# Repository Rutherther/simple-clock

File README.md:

# Simple clock
This is just a small project that aims to make a simple clock, using STM32F103C8T6.
The clock will be shown on a seven segment display. There will be multiple modes to show
on the clock display.

## HW
STM32F103C8T6 is used as the _brains_. It has RTC that may be powered by CR2032 battery.
It's connected to a USB header, allowing to communicate with a computer. The chip is capable
of being a device, only, not host.
There is a header with 3V3, SWDIO, SWCLK, GND to allow programming the chip using a tool such as STLink.
ASM1117-3.3 is used for stepping down from 5V to 3V3.
3V3 should not be connected whilst USB is connected as well. This would short output of the LDO to 3V3.
There is no protection!

There are 8 seven segment displays,
4 of them are blue, 4 of them are yellow, the whole display looks like this: Y.Y.BB:BBY.Y.
(Y for yellow digit, B for blue digit)
There are 4 LEDs and 4 buttons, the LEDs are next to the buttons, making each LED "associated" with a button.
That makes it possible to light up an LED next to button, if the button is pressed etc.

The digits of the seven segment display are connected to PNP transistors.
When pulling the pin connected to the transistor low, the digit is turned on.
The pins used may be connected to timers, and PWM may be utilized to set
brightness.
Segments get turned on by being low as well.

Mapping of pins to peripherals is documented in [pins](docs/pins.md).

## Features / Roadmap

- [x] Remember date, time
  - [x] Time
  - [x] Date
- [x] Set time and date using simple interface
- [x] Switch between view modes by button
- [x] Show time, date
- [x] Adjust brightness using PWM
- [x] Auto adjust brightness based on time
- [ ] Stopwatch
- [ ] USB communication
  - [ ] Set time, Get time
  - [ ] Show arbitrary text or number on the display
  - [ ] Start stopwatch
  
## Usage
The clock has two modes, default mode, and edit mode.
Default mode displays the current time, edit mode is
for editing the current time.

### Default mode
This is entered upon reset. Upon startup,
it displays only current time as hours and minutes.

First button may change the current view, there are
four views.
1. time - hours and minutes only
2. time - with seconds
3. time and date - hours, minutes, day in month and month
4. date - year, day in month and month

The second button switches to edit mode.

Third and fourth buttons change brightness.
The brightness is normally automatically adjusted
based on the current time set on the clock.
It may be temporarily changed using these buttons.
The change will last 30 minutes.
Third button decreases brightness, fourth increases it.

### Edit mode
In the edit mode, it's possible to change the time and date.
Upon entering edit mode, hours will be selected to be changed.

The currently selected field will blink. To select the next field,
the first button should be used. The order of the fields edited is:
hours, minutes, seconds, year, month, day.

To increment or decrement the current field, second and third
buttons should be used, respectively.

To save the time and date, fourth button does the job.
It may be pressed when editing any field.

When in the edit mode, the time is paused. If you enter the
edit mode by accident, the clock will probably get behind,
because a couple of seconds will pass before you exit the edit mode.

## Images of the clock
### Front, off

### Back

### Front, with seconds

### Front, with clock and date

## What's next
Unfortunately, I did not solder the USB correctly on my board, so I cannot
currently test sending and receiving data using the USB, that is the reason
why the current program does not even support USB. In the future, the firmware
should support USB communication and a program for a computer should be made,
with some kind of CLI for communication with the board.

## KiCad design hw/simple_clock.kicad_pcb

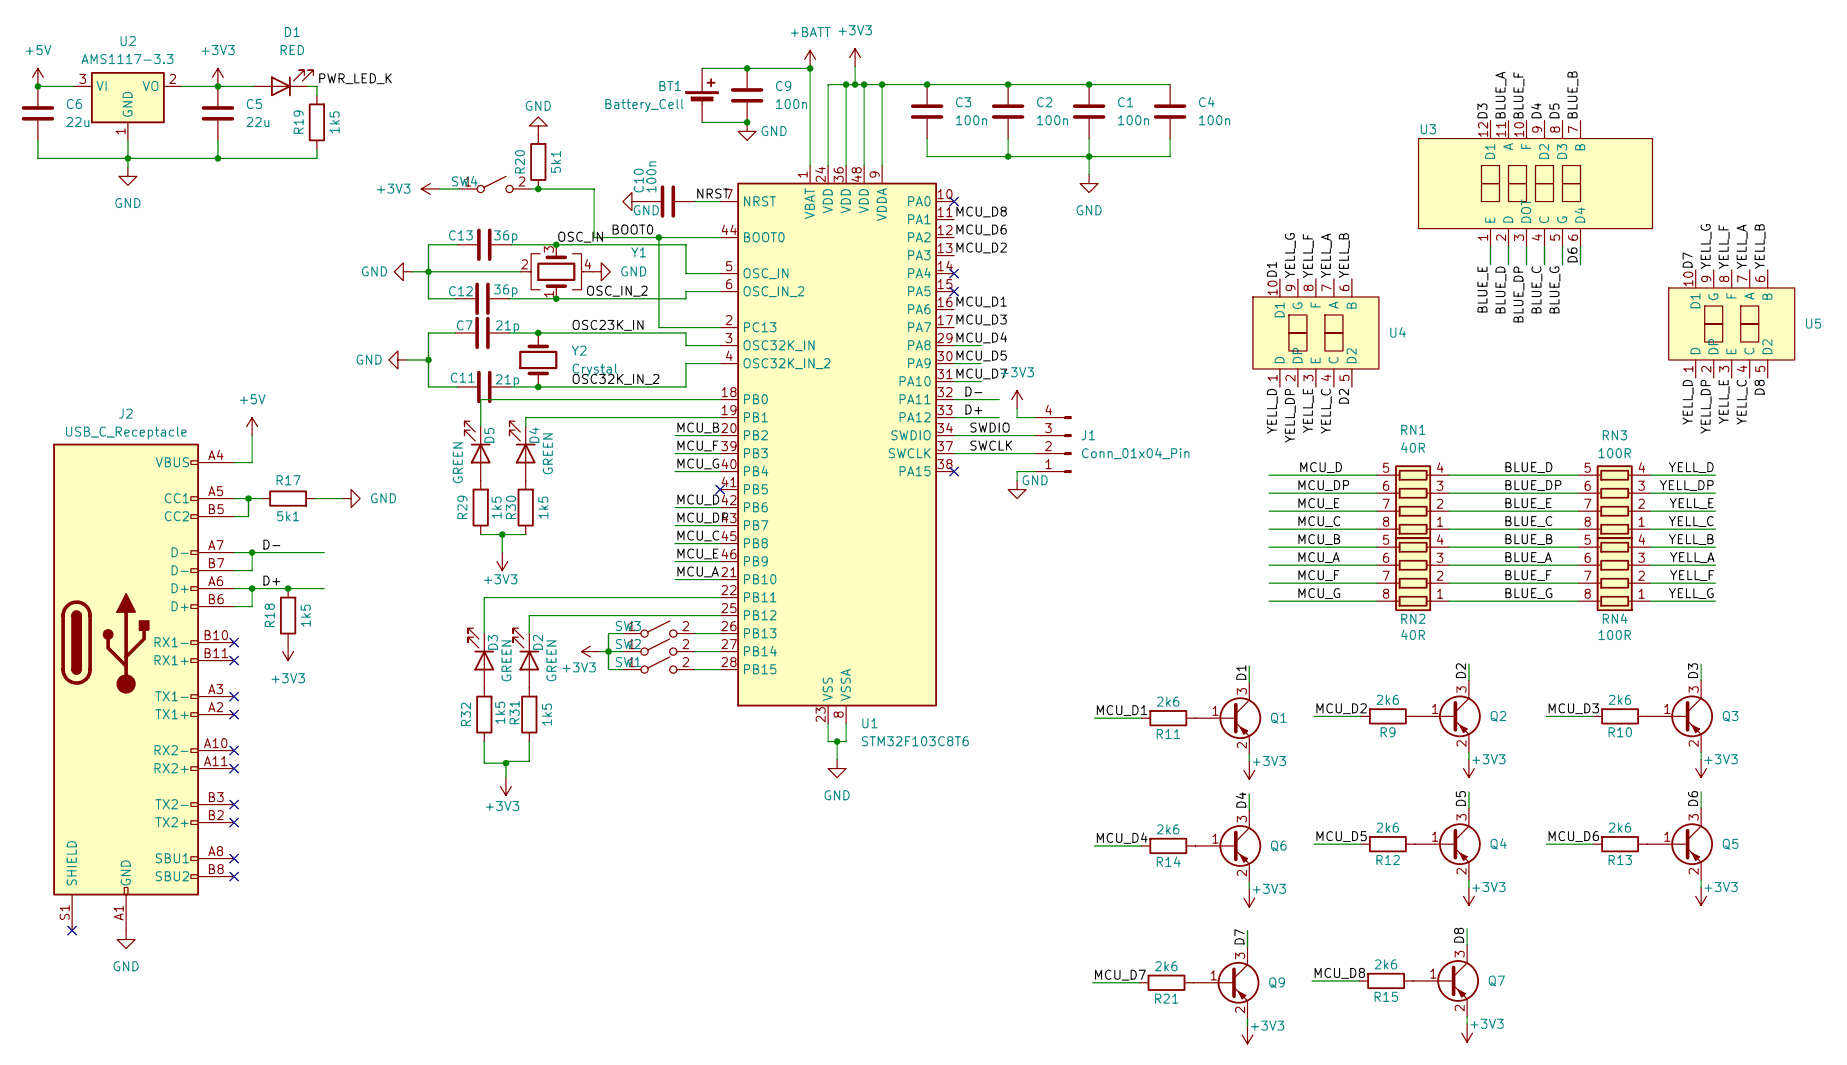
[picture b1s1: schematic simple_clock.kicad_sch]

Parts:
BT1: Battery_Cell; Q&J BS-8-1
C1, C2, C3, C4, C9, C10: 100n; C_0603_1608Metric
C5, C6: 22u; C_0603_1608Metric
C7, C11: 21p; C_0603_1608Metric
C12, C13: 36p; C_0603_1608Metric
D1: RED; LED_0603_1608Metric
D2, D3, D4, D5: GREEN; LED_0603_1608Metric
J1: Conn_01x04_Pin; PinHeader_1x04_P2.54mm_Vertical
J2: USB_C_Receptacle; USB_C_Receptacle_XKB_U262-16XN-4BVC11
Q1, Q2, Q3, Q4, Q5, Q6, Q7, Q9: Q_PNP_BEC; SOT-23
R9, R10, R11, R12, R13, R14, R15, R21: 2k6; R_0603_1608Metric
R17, R20: 5k1; R_0603_1608Metric
R18, R19, R29, R30, R31, R32: 1k5; R_0603_1608Metric
RN1, RN2: 40R; R_Array_Concave_4x0603
RN3, RN4: 100R; R_Array_Concave_4x0603
SW1, SW2, SW3, SW4: SW_SPST; TS-1088-AR02016
U1: STM32F103C8T6; LQFP-48_7x7mm_P0.5mm
U2: AMS1117-3.3; SOT-223-3_TabPin2
U3: SLR0404DBA2BD
U4, U5: SLR0402DYA3BD
Y1: Crystal_GND24; Crystal_SMD_3225-4Pin_3.2x2.5mm
Y2: Crystal; Crystal_SMD_3215-2Pin_3.2x1.5mm

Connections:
+3V3: C1.1, C2.1, C3.1, C4.1, C5.1, D1.2 (A), J1.4, Q1.2 (E), Q2.2 (E), Q3.2 (E), Q4.2 (E), Q5.2 (E), Q6.2 (E), Q7.2 (E), Q9.2 (E), R18.1, R29.1, R30.1, R31.1, R32.1, SW1.1 (A), SW2.1 (A), SW3.1 (A), SW4.1 (A), U1.9 (VDDA), U1.24 (VDD), U1.36 (VDD), U1.48 (VDD), U2.2 (VO)
+5V: C6.1, J2.A4 (VBUS), J2.A9 (VBUS), J2.B4 (VBUS), J2.B9 (VBUS), U2.3 (VI)
+BATT: BT1.1 (+), C9.1, U1.1 (VBAT)
/BLUE_A: RN2.3 (R3.1), RN4.6 (R3.2), U3.11 (A)
/BLUE_B: RN2.4 (R4.1), RN4.5 (R4.2), U3.7 (B)
/BLUE_C: RN1.1 (R1.1), RN3.8 (R1.2), U3.4 (C)
/BLUE_D: RN1.4 (R4.1), RN3.5 (R4.2), U3.2 (D)
/BLUE_DP: RN1.3 (R3.1), RN3.6 (R3.2), U3.3 (DOT)
/BLUE_E: RN1.2 (R2.1), RN3.7 (R2.2), U3.1 (E)
/BLUE_F: RN2.2 (R2.1), RN4.7 (R2.2), U3.10 (F)
/BLUE_G: RN2.1 (R1.1), RN4.8 (R1.2), U3.5 (G)
/BOOT0: R20.1, SW4.2 (B), U1.2 (PC13), U1.44 (BOOT0)
/D1: Q1.3 (C), U4.10 (D1)
/D2: Q2.3 (C), U4.5 (D2)
/D3: Q3.3 (C), U3.12 (D1)
/D4: Q6.3 (C), U3.9 (D2)
/D5: Q4.3 (C), U3.8 (D3)
/D6: Q5.3 (C), U3.6 (D4)
/D7: Q9.3 (C), U5.10 (D1)
/D8: Q7.3 (C), U5.5 (D2)
/D+: J2.A6 (D+), J2.B6 (D+), R18.2, U1.33 (PA12)
/D-: J2.A7 (D-), J2.B7 (D-), U1.32 (PA11)
/MCU_A: RN2.6 (R3.2), U1.21 (PB10)
/MCU_B: RN2.5 (R4.2), U1.20 (PB2)
/MCU_C: RN1.8 (R1.2), U1.45 (PB8)
/MCU_D: RN1.5 (R4.2), U1.42 (PB6)
/MCU_D1: R11.2, U1.16 (PA6)
/MCU_D2: R9.2, U1.13 (PA3)
/MCU_D3: R10.2, U1.17 (PA7)
/MCU_D4: R14.2, U1.29 (PA8)
/MCU_D5: R12.2, U1.30 (PA9)
/MCU_D6: R13.2, U1.12 (PA2)
/MCU_D7: R21.2, U1.31 (PA10)
/MCU_D8: R15.2, U1.11 (PA1)
/MCU_DP: RN1.6 (R3.2), U1.43 (PB7)
/MCU_E: RN1.7 (R2.2), U1.46 (PB9)
/MCU_F: RN2.7 (R2.2), U1.39 (PB3)
/MCU_G: RN2.8 (R1.2), U1.40 (PB4)
/NRST: C10.2, U1.7 (NRST)
/OSC23K_IN: C7.2, U1.3 (OSC32K_IN), Y2.2
/OSC32K_IN_2: C11.2, U1.4 (OSC32K_IN_2), Y2.1
/OSC_IN_2: C12.2, U1.6 (OSC_IN_2), Y1.1
/PWR_LED_K: D1.1 (K), R19.2
/SWCLK: J1.2, U1.37 (SWCLK)
/SWDIO: J1.3, U1.34 (SWDIO)
/YELL_A: RN4.3 (R3.1), U4.7 (A), U5.7 (A)
/YELL_B: RN4.4 (R4.1), U4.6 (B), U5.6 (B)
/YELL_C: RN3.1 (R1.1), U4.4 (C), U5.4 (C)
/YELL_D: RN3.4 (R4.1), U4.1 (D), U5.1 (D)
/YELL_DP: RN3.3 (R3.1), U4.2 (DP), U5.2 (DP)
/YELL_E: RN3.2 (R2.1), U4.3 (E), U5.3 (E)
/YELL_F: RN4.2 (R2.1), U4.8 (F), U5.8 (F)
/YELL_G: RN4.1 (R1.1), U4.9 (G), U5.9 (G)
GND: BT1.2 (-), C1.2, C2.2, C3.2, C4.2, C5.2, C6.2, C7.1, C9.2, C10.1, C11.1, C12.1, C13.1, J1.1, J2.A1 (GND), J2.A12 (GND), J2.B1 (GND), J2.B12 (GND), R17.2, R19.1, R20.2, U1.8 (VSSA), U1.23 (VSS), U1.35 (VSS), U1.47 (VSS), U2.1 (GND), Y1.2, Y1.4
unnamed: D2.2 (A), R31.2
unnamed: D2.1 (K), U1.25 (PB12)
unnamed: D3.2 (A), R32.2
unnamed: D3.1 (K), U1.22 (PB11)
unnamed: D4.2 (A), R30.2
unnamed: D4.1 (K), U1.19 (PB1)
unnamed: D5.2 (A), R29.2
unnamed: D5.1 (K), U1.18 (PB0)
unnamed: J2.A5 (CC1), J2.B5 (CC2), R17.1
unnamed: Q1.1 (B), R11.1
unnamed: Q2.1 (B), R9.1
unnamed: Q3.1 (B), R10.1
unnamed: Q4.1 (B), R12.1
unnamed: Q5.1 (B), R13.1
unnamed: Q6.1 (B), R14.1
unnamed: Q7.1 (B), R15.1
unnamed: Q9.1 (B), R21.1
unnamed: SW1.2 (B), U1.28 (PB15)
unnamed: SW2.2 (B), U1.27 (PB14)
unnamed: SW3.2 (B), U1.26 (PB13)
unnamed: C13.2, U1.5 (OSC_IN), Y1.3

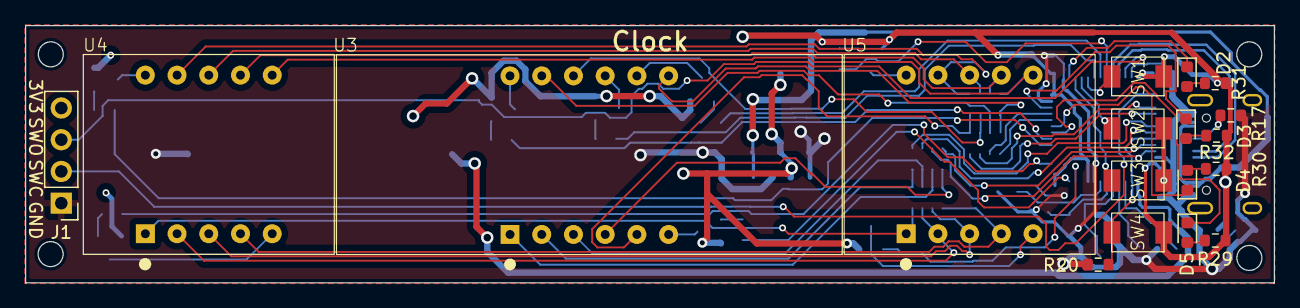
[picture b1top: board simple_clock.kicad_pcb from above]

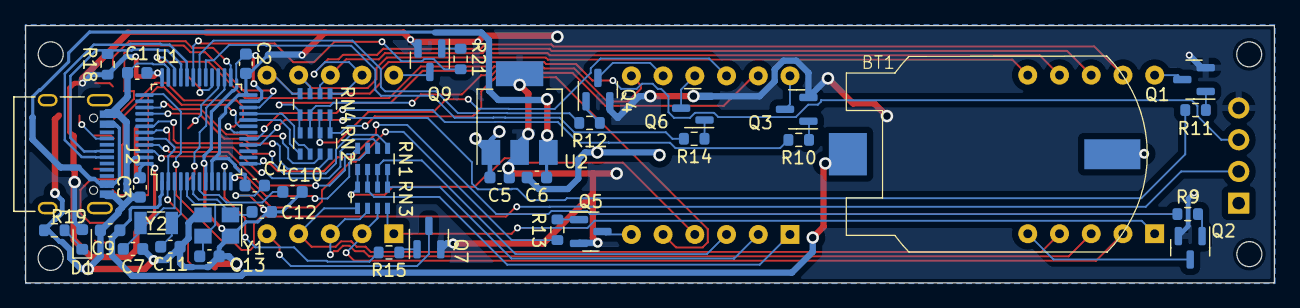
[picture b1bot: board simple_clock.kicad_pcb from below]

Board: 2 copper layers, 100.0 x 20.6 mm, 59 parts (41 on the bottom side), 75 nets.

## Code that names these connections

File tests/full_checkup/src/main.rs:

#![no_std]
#![no_main]

use core::convert::Infallible;
use embedded_hal::digital::v2::{OutputPin, InputPin};
use panic_halt as _;

use nb::block;

use cortex_m_rt::entry;
use stm32f1xx_hal::{pac, prelude::*, timer::{Timer, Tim1NoRemap, Tim2NoRemap, Tim3NoRemap, PwmChannel}, rtc::Rtc};

#[entry]
fn main() -> ! {
   // Get access to the core peripherals from the cortex-m crate
    let cp = cortex_m::Peripherals::take().unwrap();
    // Get access to the device specific peripherals from the peripheral access crate
    let dp = pac::Peripherals::take().unwrap();

    // Take ownership over the raw flash and rcc devices and convert them into the corresponding
    // HAL structs
    let mut pwr = dp.PWR;
    let mut flash = dp.FLASH.constrain();
    let rcc = dp.RCC.constrain();
    let mut backup_domain = rcc.bkp.constrain(dp.BKP, &mut pwr);

    let mut rtc = Rtc::new(dp.RTC, &mut backup_domain);

    // Freeze the configuration of all the clocks in the system and store the frozen frequencies in
    // `clocks`
    let clocks = rcc
        .cfgr
        .use_hse(8.MHz())
        .sysclk(24.MHz())
        .pclk1(24.MHz())
        .pclk2(24.MHz())
        .freeze(&mut flash.acr);

    let mut gpiob = dp.GPIOB.split();
    let mut gpioa = dp.GPIOA.split();
    let mut gpioc = dp.GPIOC.split();
    let mut afio = dp.AFIO.constrain();

    let (_, pb3, pb4) = afio.mapr.disable_jtag(gpioa.pa15, gpiob.pb3, gpiob.pb4);

    let mut led1 = gpiob.pb12.into_open_drain_output(&mut gpiob.crh);
    let mut led2 = gpiob.pb11.into_open_drain_output(&mut gpiob.crh);
    let mut led3 = gpiob.pb1.into_open_drain_output(&mut gpiob.crl);
    let mut led4 = gpiob.pb0.into_open_drain_output(&mut gpiob.crl);

    let mut leds: [&mut dyn OutputPin<Error = Infallible>; 4] = [&mut led1, &mut led2, &mut led3, &mut led4];

    let btn1 = gpiob.pb15.into_pull_down_input(&mut gpiob.crh);
    let btn2 = gpiob.pb14.into_pull_down_input(&mut gpiob.crh);
    let btn3 = gpiob.pb13.into_pull_down_input(&mut gpiob.crh);
    let btn4 = gpioc.pc13.into_floating_input(&mut gpioc.crh);

    let btns: [&dyn InputPin<Error = Infallible>; 4] = [&btn1, &btn2, &btn3, &btn4];

    let mut a = gpiob.pb10.into_open_drain_output(&mut gpiob.crh);
    let mut b = gpiob.pb2.into_open_drain_output(&mut gpiob.crl);
    let mut c = gpiob.pb8.into_open_drain_output(&mut gpiob.crh);
    let mut d = gpiob.pb6.into_open_drain_output(&mut gpiob.crl);
    let mut e = gpiob.pb9.into_open_drain_output(&mut gpiob.crh);
    let mut f = pb3.into_open_drain_output(&mut gpiob.crl);
    let mut g = pb4.into_open_drain_output(&mut gpiob.crl);
    let mut dpp = gpiob.pb7.into_open_drain_output(&mut gpiob.crl);

    let mut segments: [&mut dyn OutputPin<Error = Infallible>; 8] = [&mut a, &mut b, &mut c, &mut d, &mut e, &mut f, &mut g, &mut dpp];

    let dig1 = gpioa.pa6.into_alternate_open_drain(&mut gpioa.crl);
    let dig2 = gpioa.pa3.into_alternate_open_drain(&mut gpioa.crl);
    let dig3 = gpioa.pa7.into_alternate_open_drain(&mut gpioa.crl);
    let dig4 = gpioa.pa8.into_alternate_open_drain(&mut gpioa.crh);
    let dig5 = gpioa.pa9.into_alternate_open_drain(&mut gpioa.crh);
    let dig6 = gpioa.pa2.into_alternate_open_drain(&mut gpioa.crl);
    let dig7 = gpioa.pa10.into_alternate_open_drain(&mut gpioa.crh);
    let dig8 = gpioa.pa1.into_alternate_open_drain(&mut gpioa.crl);

    let tim1 = Timer::new(dp.TIM1, &clocks);
    let tim2 = Timer::new(dp.TIM2, &clocks);
    let tim3 = Timer::new(dp.TIM3, &clocks);

    let pins1 = (dig4, dig5, dig7);
    let pwm1 = tim1
        .pwm_hz::<Tim1NoRemap, _, _>(pins1, &mut afio.mapr, 500.Hz());

    let pins2 = (dig8, dig6, dig2);
    let pwm2 = tim2
        .pwm_hz::<Tim2NoRemap, _, _>(pins2, &mut afio.mapr, 500.Hz());

    let pins3 = (dig1, dig3);
    let pwm3 = tim3
        .pwm_hz::<Tim3NoRemap, _, _>(pins3, &mut afio.mapr, 500.Hz());

    let (mut dig4, mut dig5, mut dig7) = pwm1.split();
    let (mut dig8, mut dig6, mut dig2) = pwm2.split();
    let (mut dig1, mut dig3) = pwm3.split();

    let mut digits: [&mut dyn _embedded_hal_PwmPin<Duty = u16>; 8] = [ &mut dig1, &mut dig2, &mut dig3, &mut dig4, &mut dig5, &mut dig6, &mut dig7, &mut dig8 ];
    for digit in digits.iter_mut() {
        // has to be enabled, when disabled, 0 is outputted, meaning digit is turned on...
        digit.enable();
        digit.set_duty(0xFFFF);
    }

    // Configure the syst timer to trigger an update every second
    let mut timer = Timer::new(dp.TIM4, &clocks).counter_hz();
    timer.start(1.Hz()).unwrap();

    let mut led_index: usize = 0;
    let mut display_stage: bool = false;
    let mut digit_index: usize = 0;
    let mut segment_index: usize = 0;
    loop {
        for (i, led) in leds.iter_mut().enumerate() {
            if i == led_index {
                led.set_low().unwrap();
            } else {
                led.set_high().unwrap();
            }
        }

        for (i, btn) in btns.iter().enumerate() {
            if btn.is_high().unwrap() {
                leds[i].set_low().unwrap(); // turn on led that is next to the button
            }
        }

        for (i, digit) in digits.iter_mut().enumerate() {
            if i == digit_index {
                digit.set_duty(0);
            } else {
                digit.set_duty(0xFFFF);
            }
        }

        if display_stage {
            for (i, segment) in segments.iter_mut().enumerate() {
                if i == segment_index {
                    segment.set_low().unwrap();
                } else {
                    segment.set_high().unwrap();
                }
            }
        } else {
            for segment in segments.iter_mut() {
                segment.set_low().unwrap();
            }
        }

        led_index = (led_index + 1) % leds.len();

        if display_stage {
            segment_index = (segment_index + 1) % segments.len();
            if segment_index == 0 {
                digit_index = (digit_index + 1) % digits.len();
            }
        } else {
            digit_index = (digit_index + 1) % digits.len();
            segment_index = 0;
        }

        if segment_index == 0 && digit_index == 0 {
            display_stage = !display_stage;
        }

        block!(timer.wait()).unwrap();
    }
}

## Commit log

2023-07-29 chore(src): add essential project files
2023-07-29 feat(src): add clock seven segment display support
2023-07-29 feat(src): add CountDown abstraction
2023-07-29 feat(src): add app state with calendar
2023-07-29 feat(src): add basic button representation
2023-07-29 feat(src): add module for linear interpolation
2023-07-29 feat(src): add brightness manager
2023-07-29 feat(src): add clock application and initialization
2023-07-29 chore(src): move source to source/ folder
2023-07-29 chore: move .gitignore to root
2023-07-29 feat(tests): add rtc counter test
2023-07-29 feat(tests): add full checkup testing peripherals
    Tests all peripherals, observation should point
    out to where an error is, if any.
2023-07-29 chore: add MIT LICENSE
2023-07-30 feat(hw): add KiCAD project, schema and pcb
2023-07-30 fix(src): remove unnecessary import
2023-08-04 docs: add basic documentation
    Adds a readme, with images of the product,
    mapping of the pins to peripherals,
    the readme contains a roadmap and
    description of the hardware used.
2023-08-06 feat(src): split main into multiple functions
2023-08-06 chore(src): format with fmt
2023-08-06 feat(src): implement Calendar::from_ticks for arbitrary year, add Calendar::to_ticks
    So far, Calendar::from_ticks could not correctly parse
    other month than the base month, this commit fixes that.
    Calendar::to_ticks may convert any Calendar date to seconds passed from
    the base year. The base year is remembered in Calendar instance.
2023-08-06 tests(src): add tests for calendar tick functions
2023-08-06 feat(src): add setter methods for Calendar
    Allows to change the current date of
    already existing calendar.
2023-08-06 feat(src): replace DisplayView with hide, show on clock parts
    The clock is meant to show only clock, so introducing
    DisplayView trait was an overkill, a simpler
    solution has been implemented instead.
    Previous solution did not allow for showing and hiding individual parts,
    hiding parts may be useful when setting time, to blink the current part
    being set.
2023-08-06 feat(src): add calendar freezing possibility
2023-08-06 feat(src): add meaningful message to panic in Calendar::days_in_month
2023-08-06 chore(src): format with cargo-fmt
2023-08-07 feat(src): turn off autobrightness adjustment after manual adjustment
2023-08-08 feat(src): add clock edit mode
    Adds modes for the clock app, that may be
    changed. The new mode added is clock edit mode,
    that adds support for editing the current clock.
2023-08-08 docs: document new changes
2023-08-08 docs: add usage guide
